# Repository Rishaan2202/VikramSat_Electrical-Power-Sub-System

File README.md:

# VikramSat.v0 EPS Journal!!!
<br>
<h3>Yooooo!!! It's me, Rishaan Sharma, a 14 year old Indian boy making a satellite with 4 of my teammates.
<br>
The Satellite is named as 'VikramSat'. It's a 2U CubeSat and yeah it's quite a cool project!
<br>
<br>
I have been assigned the duty to make a fully functional Electrical Power Sub-System (EPS) for the CubeSat.
<br>
<br>
So, I'm writing this journal which notifies about the progress regularly.
<br>
I hope you all will find this quite interesting. For more details do view JOURNAL.md in this repository containing the journal.</h3>
<br>
<br>
<h3>So, you might have gone throught JOURNAL.md, pretty interesting, right? Well, here is the Schematic of the EPS:-</h3>

<br>
<br>
<h3>Boom!!! It's Vampire Theme. I hope you like it. Here comes the PCB:-</h3>

<br>
<br>
<h3>Well, take a look at the 'Power Monster':-</h3>

<br>
<br>
<h3>You wanna see the BOM:-</h3>

<br>
<br>
<h3>Here's the Screenshot of the Cart for both LCSC and JLCPCB:-</h3>

<br>
<h3>I hope you like them, well I couldn't do this better than that, cause I'm just a beginner!!!</h3>

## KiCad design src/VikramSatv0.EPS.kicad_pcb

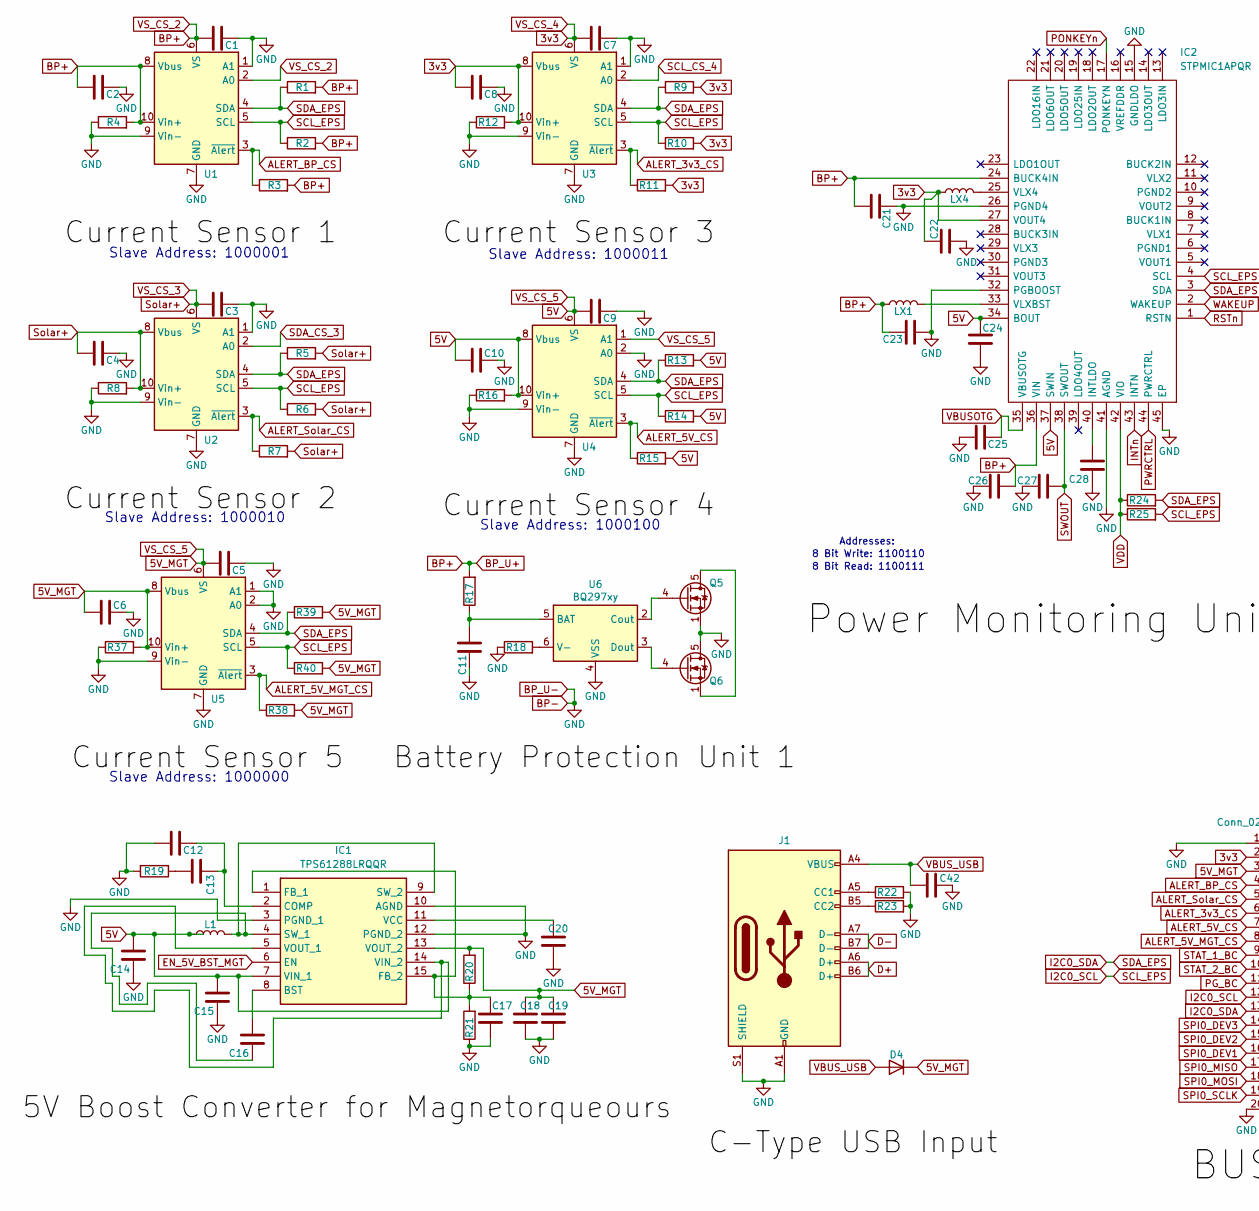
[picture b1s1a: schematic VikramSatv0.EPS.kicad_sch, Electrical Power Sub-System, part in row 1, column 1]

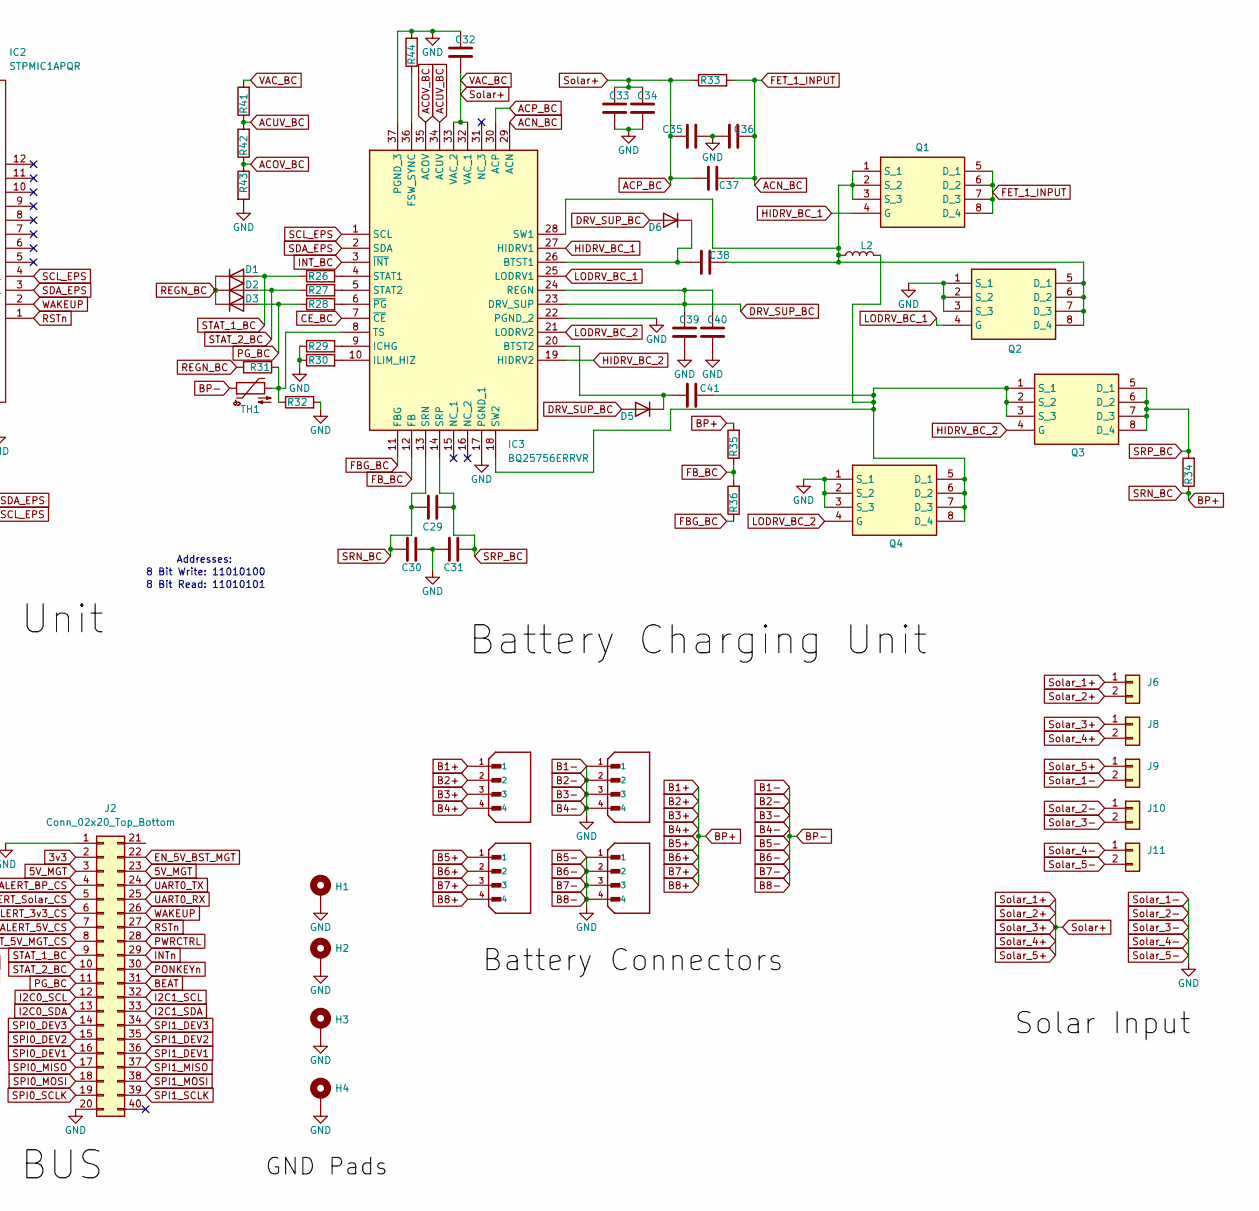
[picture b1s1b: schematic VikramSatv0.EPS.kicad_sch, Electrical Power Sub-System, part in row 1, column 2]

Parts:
C1, C2, C3, C4, C5, C6, C7, C8, C9, C10, C11, C12, C15, C16, C17, C20, C29, C30, C31, C38, C41: 0.1uF; C_0402_1005Metric
C13: 1nF; C_0402_1005Metric
C14, C21, C22, C23, C24: 10uF; C_0805_2012Metric
C18, C19: 22uF; C_0402_1005Metric
C25, C26, C28, C39, C40: 4.7uF; C_0402_1005Metric
C27: 220uF; C_1206_3216Metric
C32, C42: 1uF; C_0402_1005Metric
C33, C34: 100uF; C_0805_2012Metric
C35, C36, C37: 470nF; C_0402_1005Metric
D1, D2, D3, D4, D5, D6: 1N4148WT; D_SOD-523
H1, H2, H3, H4: MountingHole_Pad; MountingHole_3mm_Pad_Via
IC1: TPS61288LRQQR; TPS61288; Mouser Part Number 595-TPS61288LRQQR
IC2: STPMIC1APQR; STPMIC1A; Mouser Part Number 511-STPMIC1APQR
IC3: BQ25756ERRVR; QFN50P500X600X100-37N-D; Mouser Part Number 595-BQ25756ERRVR
J1: USB_C_Receptacle_USB2.0_14P; USB_C_Receptacle_HRO_TYPE-C-31-M-12
J2: Conn_02x20_Top_Bottom; PinHeader_2x20_P2.54mm_Vertical
J3, J4, J5, J7: B4B-XH-A; JST_B4B-XH-A
J6, J8, J9, J10, J11: Conn_01x02; PinHeader_2x01_P2.54mm_Vertical
L1: 2.2uH; L_0402_1005Metric
L2: 10uH; L_0201_0603Metric
LX1, LX4: 1uH; L_0402_1005Metric
Q1, Q2, Q3, Q4: Mosfet 20A, 30V; Mouser Part Number 78-SISA14DN-T1-GE3
Q5, Q6: CSD16401Q5; TDSON-8-1
R1, R2, R5, R6, R9, R10, R13, R14, R24, R25, R39, R40: 4.7kΩ; R_0402_1005Metric
R3, R7, R11, R15, R22, R23, R26, R27, R28, R38: 10kΩ; R_0402_1005Metric
R4, R8, R12, R16, R37: 4mΩ; R_0402_1005Metric
R17: 330Ω; R_0402_1005Metric
R18: 2.2kΩ; R_0402_1005Metric
R19: 36.5kΩ; R_0402_1005Metric
R20: 105kΩ; R_0402_1005Metric
R21: 14.3kΩ; R_0402_1005Metric
R29: 4.22kΩ; R_0402_1005Metric
R30: 19.1kΩ; R_0402_1005Metric
R31: 5.23kΩ; R_0402_1005Metric
R32: 30.1kΩ; R_0402_1005Metric
R33: 1mΩ; R_0402_1005Metric
R34: 5mΩ; R_0402_1005Metric
R35: 174kΩ; R_0402_1005Metric
R36: 100kΩ; R_0402_1005Metric
R41: 357kΩ; R_0402_1005Metric
R42: 75kΩ; R_0402_1005Metric
R43: 22.6kΩ; R_0402_1005Metric
R44: 133kΩ; R_0402_1005Metric
TH1: 10kΩ NTC; R_0402_1005Metric
U1, U2, U3, U4, U5: INA226; VSSOP-10_3x3mm_P0.5mm
U6: BQ297xy; WSON-6_1.5x1.5mm_P0.5mm

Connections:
3v3: C7.2, C8.2, C22.1, IC2.27 (VOUT4), J2.2, LX4.1, R9.2, R10.2, R11.2, R12.2, U3.6 (VS), U3.8 (Vbus), U3.10 (Vin+)
5V: C5.2, C6.2, C9.2, C10.2, C14.2, C15.2, C18.2, C19.2, C24.1, D4.1 (K), IC1.5 (VOUT_1), IC1.7 (VIN_1), IC1.13 (VOUT_2), IC1.14 (VIN_2), IC2.34 (BOUT), IC2.37 (SWIN), J2.3, J2.23, L1.1, R13.2, R14.2, R15.2, R16.2, R20.2, R37.2, R38.2, R39.2, R40.2, U4.1 (A1), U4.6 (VS), U4.8 (Vbus), U4.10 (Vin+), U5.6 (VS), U5.8 (Vbus), U5.10 (Vin+)
ACN_BC: C36.2, C37.1, IC3.29 (ACN), Q1.5 (D_1), Q1.6 (D_2), Q1.7 (D_3), Q1.8 (D_4), R33.2
ACOV_BC: IC3.35 (ACOV), R42.1, R43.1
ACP_BC: C3.2, C4.2, C32.1, C33.2, C34.2, C35.1, C37.2, IC3.30 (ACP), IC3.32 (VAC_1), IC3.33 (VAC_2), J6.1, J6.2, J8.1, J8.2, J9.1, R5.2, R6.2, R7.2, R8.2, R33.1, R41.2, U2.6 (VS), U2.8 (Vbus), U2.10 (Vin+)
ACUV_BC: IC3.34 (ACUV), R41.1, R42.2
ALERT_3v3_CS: J2.6, R11.1, U3.3 (~Alert)
ALERT_5V_CS: J2.7, R15.1, U4.3 (~Alert)
ALERT_5V_MGT_CS: J2.8, R38.1, U5.3 (~Alert)
ALERT_BP_CS: J2.4, R3.1, U1.3 (~Alert)
ALERT_Solar_CS: J2.5, R7.1, U2.3 (~Alert)
B1+: C1.2, C2.2, C21.2, C23.1, C26.2, C29.1, C30.1, IC2.24 (BUCK4IN), IC2.36 (VIN), IC3.13 (SRN), J4.1, J4.2, J4.3, J4.4, J7.1, J7.2, J7.3, J7.4, LX1.1, R1.2, R2.2, R3.2, R4.2, R17.2, R34.1, R35.2, U1.2 (A0), U1.6 (VS), U1.8 (Vbus), U1.10 (Vin+)
B1-: C1.1, C2.1, C3.1, C4.1, C5.1, C6.1, C7.1, C8.1, C9.1, C10.1, C11.1, C12.2, C14.1, C15.1, C17.1, C18.1, C19.1, C20.1, C21.1, C22.2, C23.2, C24.2, C25.1, C26.1, C27.1, C28.1, C30.2, C31.1, C32.2, C33.1, C34.1, C35.2, C36.1, C39.1, C40.1, C42.2, H1.1, H2.1, H3.1, H4.1, IC1.3 (PGND_1), IC1.10 (AGND), IC1.12 (PGND_2), IC2.15 (GNDLDO), IC2.26 (PGND4), IC2.32 (PGBOOST), IC2.41 (AGND), IC2.45 (EP), IC3.17 (PGND_1), IC3.22 (PGND_2), IC3.37 (PGND_3), J1.A1 (GND), J1.A12 (GND), J1.B1 (GND), J1.B12 (GND), J1.S1 (SHIELD), J2.1, J2.20, J3.1, J3.2, J3.3, J3.4, J5.1, J5.2, J5.3, J5.4, J9.2, J10.1, J10.2, J11.1, J11.2, Q2.1 (S_1), Q2.2 (S_2), Q2.3 (S_3), Q4.1 (S_1), Q4.2 (S_2), Q4.3 (S_3), Q5.1 (S), Q5.2 (S), Q5.3 (S), Q6.5 (D), R4.1, R8.1, R12.1, R16.1, R18.1, R19.2, R21.1, R22.2, R23.2, R29.1, R30.1, R32.2, R37.1, R43.2, R44.2, TH1.1, U1.1 (A1), U1.7 (GND), U1.9 (Vin-), U2.1 (A1), U2.7 (GND), U2.9 (Vin-), U3.1 (A1), U3.7 (GND), U3.9 (Vin-), U4.2 (A0), U4.7 (GND), U4.9 (Vin-), U5.1 (A1), U5.2 (A0), U5.7 (GND), U5.9 (Vin-), U6.4 (VSS)
BEAT: J2.31
CE_BC: IC3.7 (~CE)
D+: J1.A6 (D+), J1.B6 (D+)
D-: J1.A7 (D-), J1.B7 (D-)
DRV_SUP_BC: C39.2, C40.2, D5.2 (A), D6.2 (A), IC3.23 (DRV_SUP), IC3.24 (REGN)
EN_5V_BST_MGT: IC1.6 (EN), J2.22
FBG_BC: IC3.11 (FBG), R36.1
FB_BC: IC3.12 (FB), R35.1, R36.2
HIDRV_BC_1: IC3.27 (HIDRV1), Q1.4 (G)
HIDRV_BC_2: IC3.19 (HIDRV2), Q3.4 (G)
I2C0_SCL: IC2.4 (SCL), IC3.1 (SCL), J2.12, R2.1, R6.1, R10.1, R14.1, R25.2, R40.1, U1.5 (SCL), U2.5 (SCL), U3.5 (SCL), U4.5 (SCL), U5.5 (SCL)
I2C0_SDA: IC2.3 (SDA), IC3.2 (SDA), J2.13, R1.1, R5.1, R9.1, R13.1, R24.2, R39.1, U1.4 (SDA), U2.4 (SDA), U3.4 (SDA), U4.4 (SDA), U5.4 (SDA)
I2C1_SCL: J2.32
I2C1_SDA: J2.33
INT_BC: IC3.3 (~INT)
INTn: IC2.43 (INTN), J2.29
LODRV_BC_1: IC3.25 (LODRV1), Q2.4 (G)
LODRV_BC_2: IC3.21 (LODRV2), Q4.4 (G)
unnamed: C13.2, R19.1
unnamed: C41.1, D5.1 (K), IC3.20 (BTST2)
unnamed: C38.1, D6.1 (K), IC3.26 (BTST1)
unnamed: C16.2, IC1.8 (BST)
unnamed: C12.1, C13.1, IC1.2 (COMP)
unnamed: C17.2, IC1.1 (FB_1), IC1.15 (FB_2), R20.1, R21.2
unnamed: C16.1, IC1.4 (SW_1), IC1.9 (SW_2), L1.2
unnamed: C20.2, IC1.11 (VCC)
unnamed: C28.2, IC2.40 (INTLDO)
unnamed: IC2.25 (VLX4), LX4.2
unnamed: IC2.33 (VLXBST), LX1.2
unnamed: IC3.36 (FSW_SYNC), R44.1
unnamed: IC3.9 (ICHG), R29.2
unnamed: IC3.10 (ILIM_HIZ), R30.2
unnamed: IC3.4 (STAT1), R26.2
unnamed: IC3.5 (STAT2), R27.2
unnamed: C38.2, IC3.28 (SW1), L2.1, Q1.1 (S_1), Q1.2 (S_2), Q1.3 (S_3), Q2.5 (D_1), Q2.6 (D_2), Q2.7 (D_3), Q2.8 (D_4)
unnamed: C41.2, IC3.18 (SW2), L2.2, Q3.1 (S_1), Q3.2 (S_2), Q3.3 (S_3), Q4.5 (D_1), Q4.6 (D_2), Q4.7 (D_3), Q4.8 (D_4)
unnamed: IC3.8 (TS), R31.1, R32.1, TH1.2
unnamed: IC3.6 (~PG), R28.2
unnamed: J1.A5 (CC1), R22.1
unnamed: J1.B5 (CC2), R23.1
unnamed: Q5.5 (D), Q6.1 (S), Q6.2 (S), Q6.3 (S)
unnamed: Q5.4 (G), U6.2 (Cout)
unnamed: Q6.4 (G), U6.3 (Dout)
unnamed: C11.2, R17.1, U6.5 (BAT)
unnamed: R18.2, U6.6 (V-)
PG_BC: D3.2 (A), J2.11, R28.1
PONKEYn: IC2.17 (PONKEYN), J2.30
PWRCTRL: IC2.44 (PWRCTRL), J2.28
REGN_BC: D1.1 (K), D2.1 (K), D3.1 (K), R31.2
RSTn: IC2.1 (RSTN), J2.27
SCL_CS_4: U3.2 (A0)
SDA_CS_3: U2.2 (A0)
SPI0_DEV1: J2.16
SPI0_DEV2: J2.15
SPI0_DEV3: J2.14
SPI0_MISO: J2.17
SPI0_MOSI: J2.18
SPI0_SCLK: J2.19
SPI1_DEV1: J2.36
SPI1_DEV2: J2.35
SPI1_DEV3: J2.34
SPI1_MISO: J2.37
SPI1_MOSI: J2.38
SPI1_SCLK: J2.39
SRP_BC: C29.2, C31.2, IC3.14 (SRP), Q3.5 (D_1), Q3.6 (D_2), Q3.7 (D_3), Q3.8 (D_4), R34.2
STAT_1_BC: D1.2 (A), J2.9, R26.1
STAT_2_BC: D2.2 (A), J2.10, R27.1
SWOUT: C27.2, IC2.38 (SWOUT)
UART0_RX: J2.25
UART0_TX: J2.24
VBUSOTG: C25.2, IC2.35 (VBUSOTG)
VBUS_USB: C42.1, D4.2 (A), J1.A4 (VBUS), J1.A9 (VBUS), J1.B4 (VBUS), J1.B9 (VBUS)
VDD: IC2.42 (VIO), R24.1, R25.1
WAKEUP: IC2.2 (WAKEUP), J2.26

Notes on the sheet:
8 Bit Write: 11010100
8 Bit Read: 1100111
8 Bit Read: 11010101
Slave Address: 1000010
Slave Address: 1000001
Slave Address: 1000000
Slave Address: 1000011
8 Bit Write: 1100110
Addresses:
Slave Address: 1000100

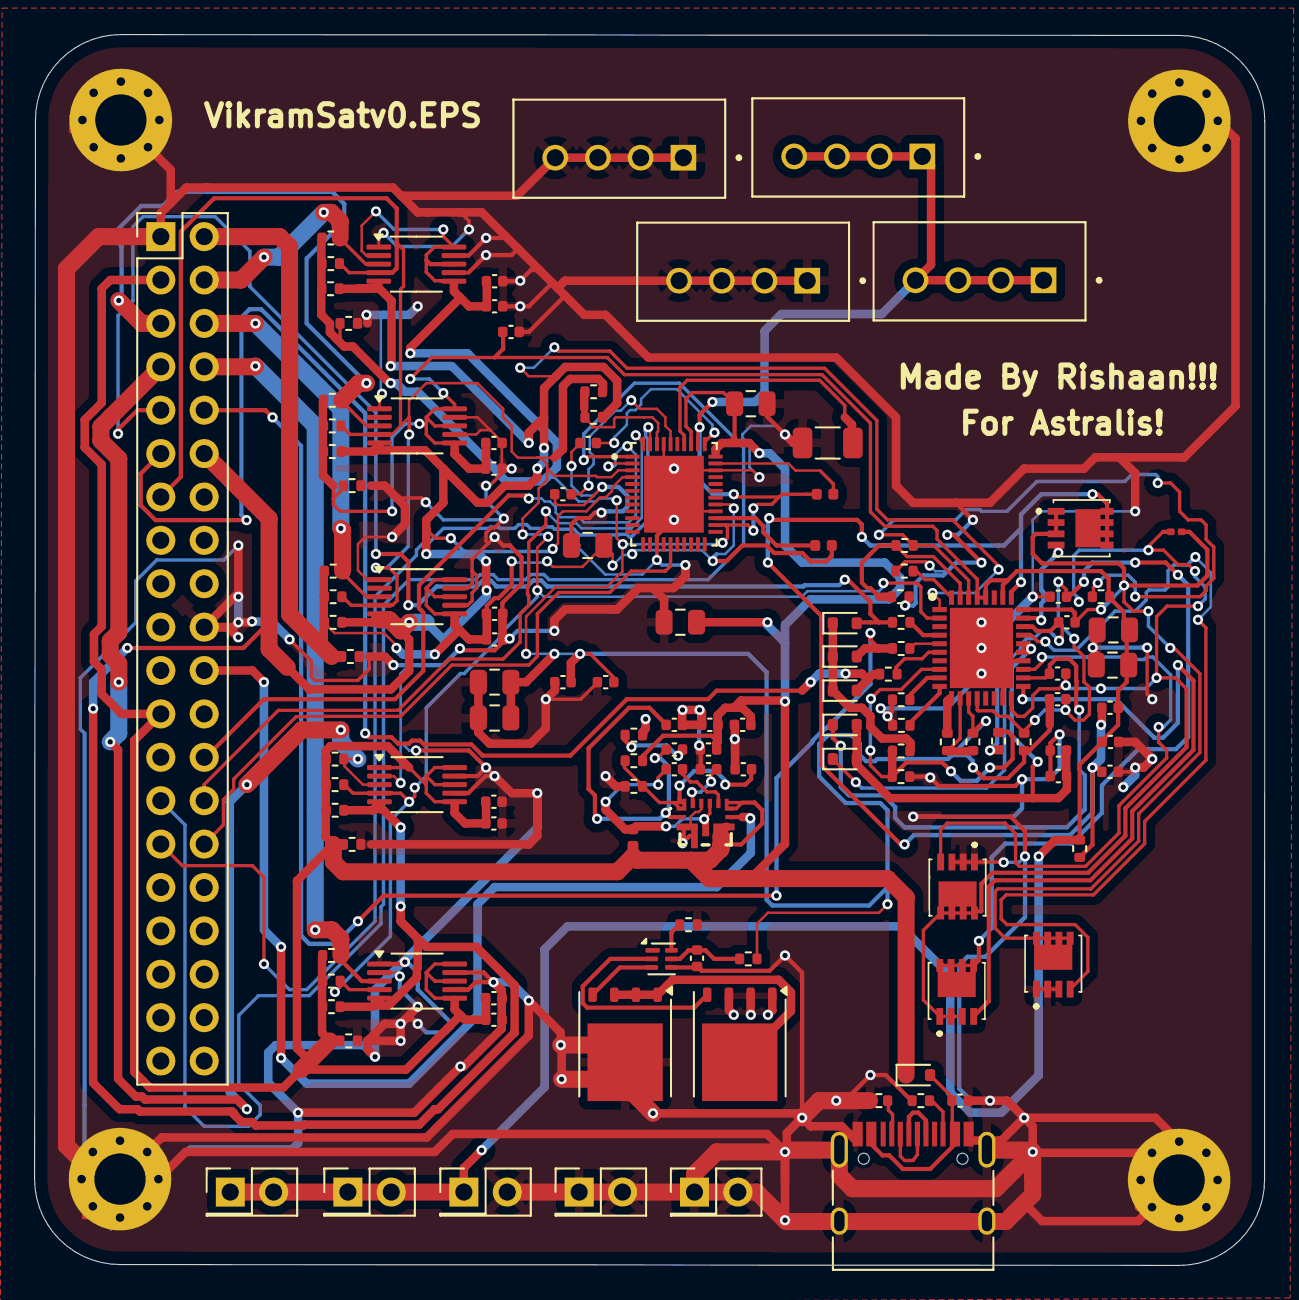
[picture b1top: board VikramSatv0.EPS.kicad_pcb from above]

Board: 2 copper layers, 72.0 x 72.0 mm, 127 parts (0 on the bottom side), 66 nets.

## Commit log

2025-07-01 Create JOURNAL.md
    No need of description, it's just a starting!!!
2025-07-01 JOURNAL.md
2025-07-23 LICENSE
2025-07-23 README.md
2025-09-17 schematic.pdf
2025-09-17 Add files via upload
    The Official Schematic of VikramSatv0.EPS!!!
2025-09-18 VikramSatv0.EPS
2025-09-18 Create Yoo!!!
2025-09-20 Create Hi!!!
2025-09-20 Rename VikramSatv0.EPS.Schematic.pdf to schematic.pdf
2025-09-20 Rename Screenshot 2025-09-20 161941.png to cart.png
2025-09-21 Create New!!!
2025-09-21 Rename Screenshot 2025-09-21 213551.png to JLCPCB.cart.png
2025-09-21 Rename Screenshot 2025-09-21 214011.png to LCSC.cart.png
2025-09-21 Create Hello!!!
2025-09-22 Rename Screenshot 2025-09-22 090605.png to LCSC.cart.png
2025-09-22 Rename Screenshot 2025-09-22 090605.png to LCSC.cart
2025-09-27 Rename Screenshot 2025-09-27 141404.png to JLCPCB.cart.png
2025-09-28 Update LICENSE
